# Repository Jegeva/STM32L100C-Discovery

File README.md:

# STM32L100C-Discovery

this is searching for CMSIS for arm in ../..

requires stlink to program, openocd to debug

projet template is the default blink/click demo

:)

DO NOT USE ANYTHING IN iotad victim board, THIS CODE IS INTENTIONALY VULNERABLE !

have fun

this repo contains stmicro licenced stuff, their stuff IS THEIR STUFF, not mine

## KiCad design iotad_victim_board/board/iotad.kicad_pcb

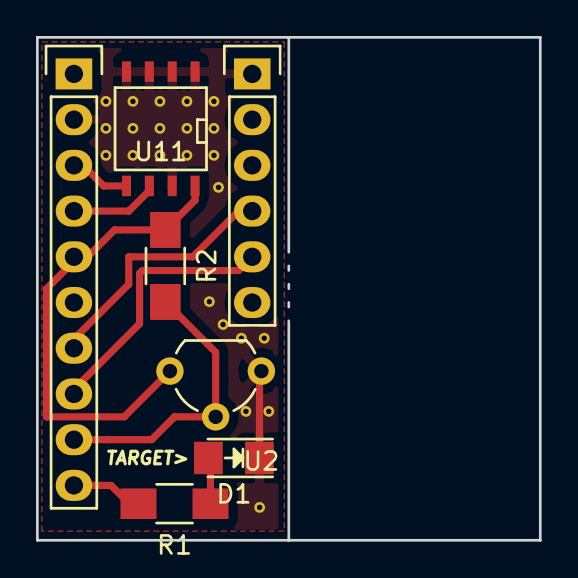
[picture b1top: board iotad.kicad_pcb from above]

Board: 2 copper layers, 27.9 x 27.9 mm, 7 parts (0 on the bottom side), 9 nets.

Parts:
D1: LED; LED_1206
P1: CONN_01X10; Pin_Header_Straight_1x10
P2: CONN_01X06; Pin_Header_Straight_1x06
R1: R; R_1206_HandSoldering
R2: 4.8k; R_1206_HandSoldering
U2: MAX31820; TO-92_Molded_Wide
U11: 24C16; SOIC-8-N

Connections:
DATA: P1.9, R2.2, U2.2
GND: D1.1, P1.2, P2.1, U2.1, U11.1, U11.2, U11.3, U11.4, U11.7
unnamed: D1.2, R1.1
unnamed: P1.10, R1.2
RX: P1.7, P2.4
SCL: P1.4, U11.6
SDA: P1.3, U11.5
TX: P1.8, P2.5
VCC: P1.5, R2.1, U2.3, U11.8

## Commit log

2016-01-29 iotad
2016-02-06 board peripherals and external components working
2016-02-07 board
2016-02-16 today
2016-02-21 splitting in files
2016-02-24 vulns in :)
2016-02-28 harcoded password
2016-03-01 ensure
2016-03-25 storing
2016-03-26 golden candidate
2016-03-28 bug squashing + comm i2c 4 jens on command
2016-04-14 sync ensure
2016-04-14 last min up
